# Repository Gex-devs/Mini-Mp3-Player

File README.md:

# Mini Mp3 Player
Mini Mp3 Player with Custom PCB

<p>Schematic view <p>

<p>Board Image<p>

<p>3d Model<p>

# Parts List

- Atmega328p-pu
- 16Mhz Crystal Oscillator
- 2x 20pF Capacitors for the Oscillator (Optional)
- 100uF Capacitor (Optional)
- Diode 1N4007 (Optional) 
- DFPlayer
- HT7333 3.3v Voltage regulator
- Small Switch
- KY040-HW Rotary encoder

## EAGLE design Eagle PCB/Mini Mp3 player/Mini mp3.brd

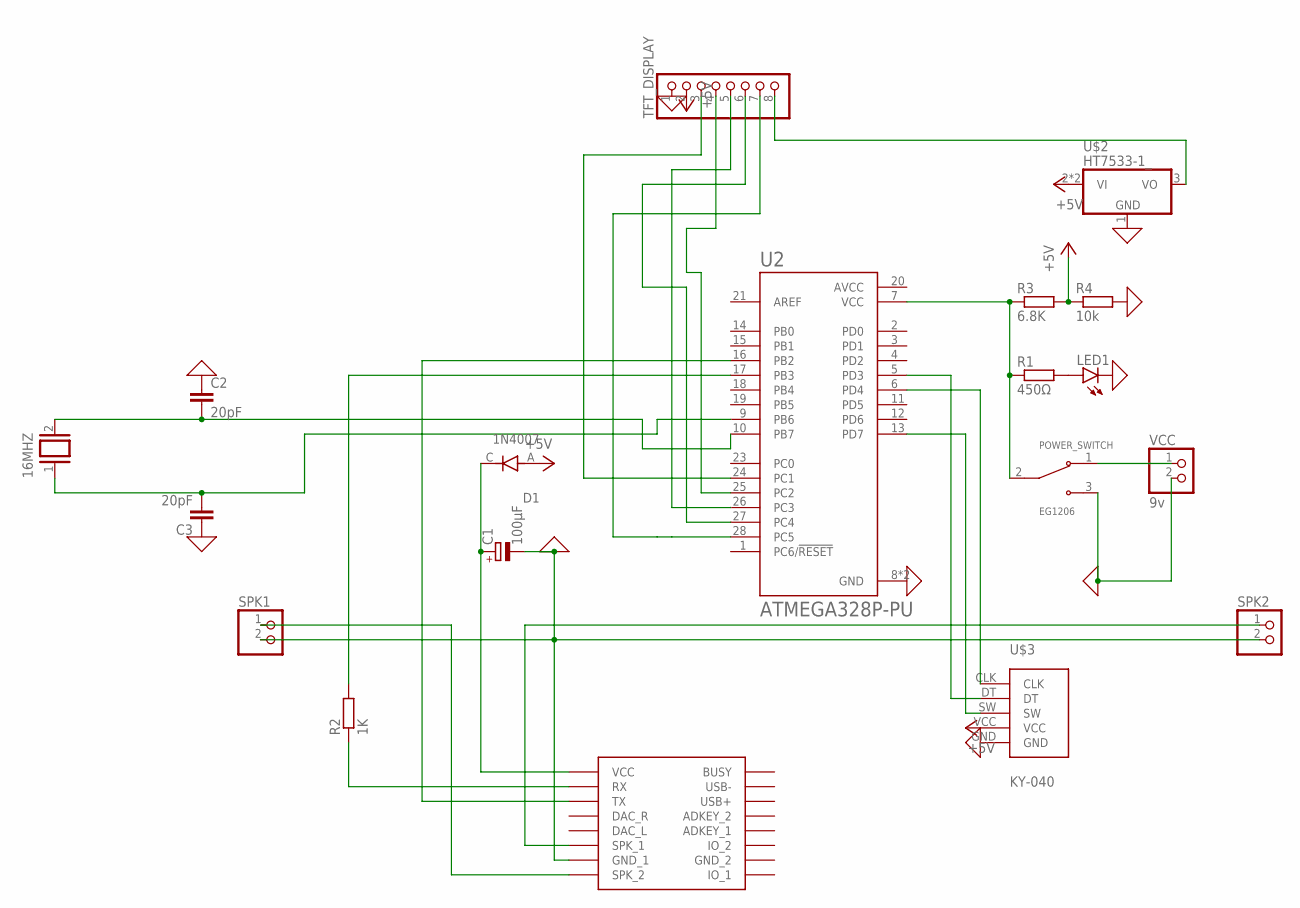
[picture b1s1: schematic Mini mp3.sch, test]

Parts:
16MHZ: XTAL/S; QS
C1: 100μF; E2,5-7
C2, C3: 20pF; C025-025X050
D1: 1N4007; DIOAD1060W80L520D270
LED1: LED5MM
POWER_SWITCH: EG1206; SW_EG1206
R1: 450Ω; 0204/7
R2: 1K; 0204/7
R3: 6.8K; 0204/7
R4: 10k; 0204/7
SPK1, SPK2: PINHD-1X2; 1X02
TFT_DISPLAY: PINHD-1X8; 1X08
U2: ATMEGA328P-PU; DIP794W46P254L2967H457Q28B
U$1: DFPLAYER
U$2: HT7533-1_; SOT89
U$3: KY-040; KY-040-PORT
VCC: 9v; 1X02

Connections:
0: C2.1, C3.1, LED1.K (C), POWER_SWITCH.3, R4.2, TFT_DISPLAY.1, U2.8 (GND), U2.22 (GND), U$2.1 (GND), U$3.GND, VCC.2
+5V: D1.A, R3.2, R4.1, TFT_DISPLAY.2, U$2.2 (VI), U$2.2@1 (VI), U$3.VCC
AVCC: U2.20 (AVCC)
unnamed: R2.2, U2.17 (PB3)
unnamed: U2.16 (PB2), U$1.TX
unnamed: TFT_DISPLAY.6, U2.27 (PC4)
unnamed: SPK1.1, U$1.SPK2 (SPK_2)
unnamed: TFT_DISPLAY.8, U$2.3 (VO)
unnamed: TFT_DISPLAY.7, U2.28 (PC5)
unnamed: TFT_DISPLAY.5, U2.26 (PC3)
unnamed: TFT_DISPLAY.4, U2.25 (PC2)
unnamed: TFT_DISPLAY.3, U2.24 (PC1)
unnamed: C1.-, SPK1.2, SPK2.2, U$1.GND_1
unnamed: C1.+, D1.C, U$1.VCC
unnamed: POWER_SWITCH.2, R1.1, R3.1, U2.7 (VCC)
unnamed: POWER_SWITCH.1, VCC.1
unnamed: R2.1, U$1.RX
unnamed: U2.13 (PD7), U$3.SW
unnamed: U2.5 (PD3), U$3.DT
unnamed: 16MHZ.2, C2.2, U2.10 (PB7)
unnamed: 16MHZ.1, C3.2, U2.9 (PB6)
unnamed: LED1.A, R1.2
unnamed: U2.6 (PD4), U$3.CLK
S: SPK2.1, U$1.SPK1 (SPK_1)

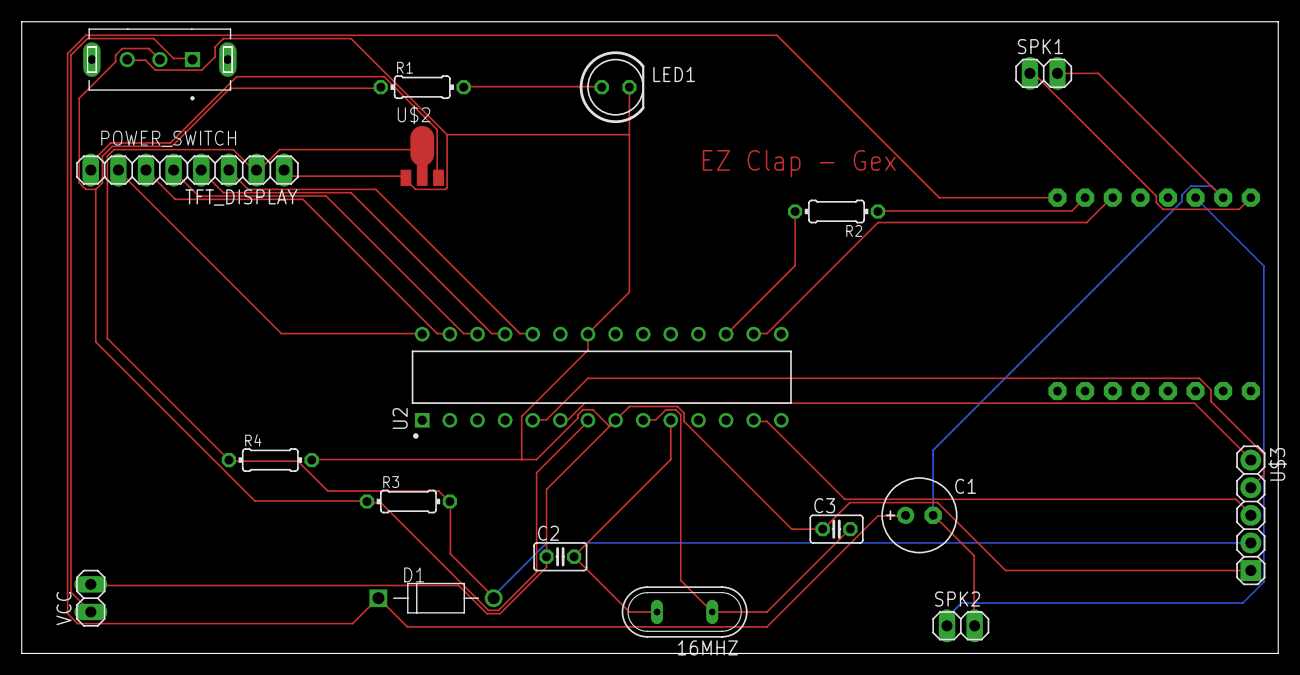
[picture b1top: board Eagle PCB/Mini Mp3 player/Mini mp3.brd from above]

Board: 2 copper layers, 115.5 x 58.1 mm, 19 parts (1 on the bottom side), 23 nets.

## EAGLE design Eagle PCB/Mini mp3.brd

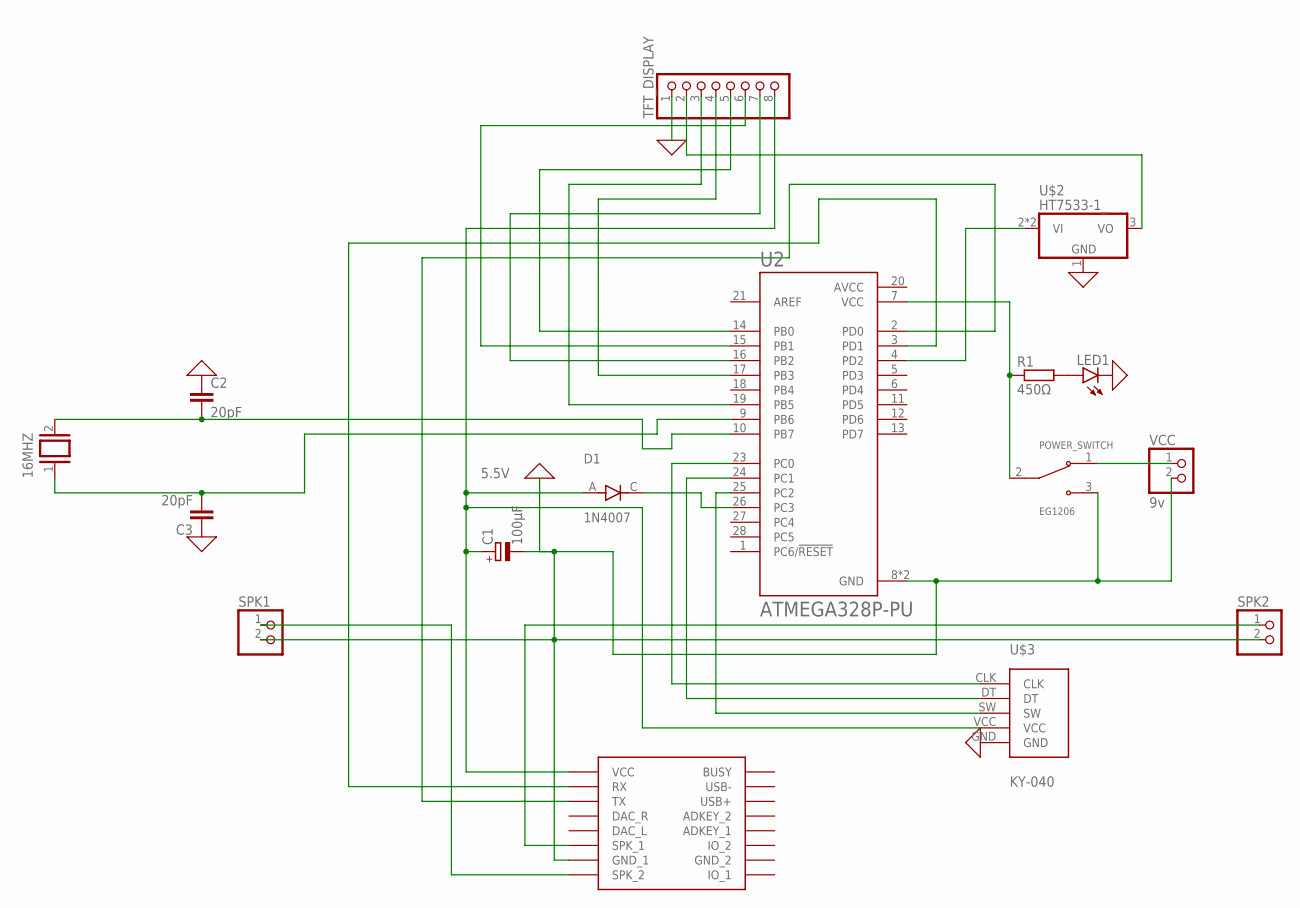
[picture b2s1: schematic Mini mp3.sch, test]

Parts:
16MHZ: XTAL/S; QS
C1: 100μF; E2,5-7
C2, C3: 20pF; C025-025X050
D1: 1N4007; DIOAD1060W80L520D270
LED1: LED5MM
POWER_SWITCH: EG1206; SW_EG1206
R1: 450Ω; 0204/7
SPK1, SPK2: PINHD-1X2; 1X02
TFT_DISPLAY: PINHD-1X8; 1X08
U2: ATMEGA328P-PU; DIP794W46P254L2967H457Q28B
U$1: DFPLAYER
U$2: HT7533-1_; SOT89
U$3: KY-040; KY-040-PORT
VCC: 9v; 1X02

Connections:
0: C1.-, C2.1, C3.1, LED1.K (C), POWER_SWITCH.3, SPK1.2, SPK2.2, TFT_DISPLAY.1, U2.8 (GND), U2.22 (GND), U$1.GND_1, U$2.1 (GND), U$3.GND, VCC.2
5.5V: C1.+, D1.A, TFT_DISPLAY.8, U$1.VCC, U$3.VCC
AVCC: U2.20 (AVCC)
unnamed: U2.3 (PD1), U$1.RX
unnamed: U2.2 (PD0), U$1.TX
unnamed: U2.23 (PC0), U$3.CLK
unnamed: SPK1.1, U$1.SPK2 (SPK_2)
unnamed: TFT_DISPLAY.2, U$2.3 (VO)
unnamed: U2.4 (PD2), U$2.2 (VI), U$2.2@1 (VI)
unnamed: TFT_DISPLAY.3, U2.19 (PB5)
unnamed: TFT_DISPLAY.4, U2.17 (PB3)
unnamed: TFT_DISPLAY.5, U2.14 (PB0)
unnamed: TFT_DISPLAY.7, U2.16 (PB2)
unnamed: TFT_DISPLAY.6, U2.15 (PB1)
unnamed: POWER_SWITCH.2, R1.1, U2.7 (VCC)
unnamed: POWER_SWITCH.1, VCC.1
unnamed: U2.24 (PC1), U$3.DT
unnamed: D1.C, U2.26 (PC3)
unnamed: U2.25 (PC2), U$3.SW
unnamed: 16MHZ.2, C2.2, U2.10 (PB7)
unnamed: 16MHZ.1, C3.2, U2.9 (PB6)
unnamed: LED1.A, R1.2
S: SPK2.1, U$1.SPK1 (SPK_1)

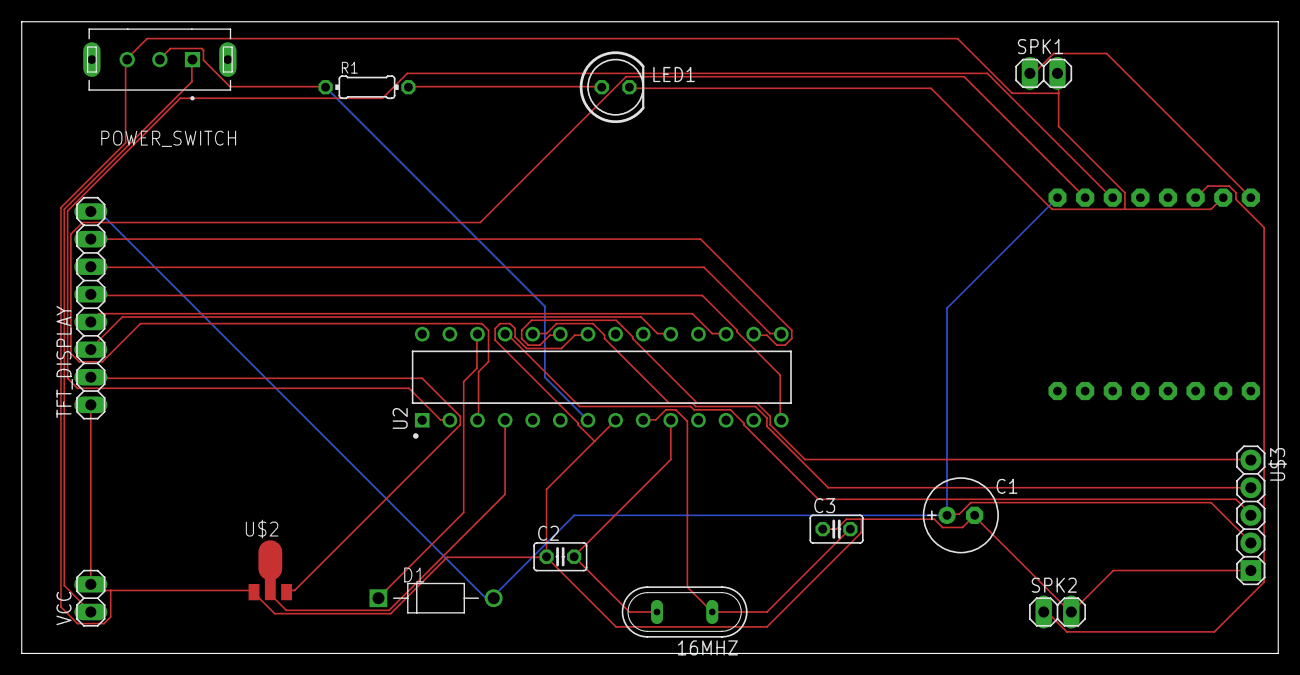
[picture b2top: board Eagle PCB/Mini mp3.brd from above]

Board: 2 copper layers, 115.5 x 58.1 mm, 16 parts (1 on the bottom side), 22 nets.

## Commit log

2023-09-09 Added Eagle PCB project
2023-09-10 updated board
2023-09-24 Voltage divider included and updated Mini display
2024-02-13 added image and updated list
2024-02-13 forgot the image
